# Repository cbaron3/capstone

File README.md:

# Capstone
Source code for Mechatronic Systems Engineering Capstone project

# Requirements

## Teensyduino

Firmware is written for a Teensy 3.2 and makes use of Teensy features such as PWMServo and elapsedMicros. 

[Teensyduino](https://www.pjrc.com/teensy/teensyduino.html)

## Barometer

Library to interact with the on-board MPL3115A2. 

[MPL3115A2](https://github.com/sparkfun/MPL3115A2_Breakout/tree/master/Libraries/Arduino)

## GPS

Libraries to interact with the on-board Adafruit GPS module. Two were selected: one interrupt-based and one polling-based. The interrupt-based library is what we use.

[Adafruit_GPS - Interrupt based](https://github.com/adafruit/Adafruit_GPS)

[TinyGPS - Polling based](https://github.com/mikalhart/TinyGPS)

## IMU

Library to interact with the on-board MPU9250.

[MPU9250](https://github.com/bolderflight/MPU9250)

## AHRS 

Library to filter our raw IMU data to produce accurate roll/pitch/yaw.

[uNavAHR](https://github.com/bolderflight/uNavAHRS)

[Eigen - Library Dependency](https://github.com/bolderflight/Eigen)

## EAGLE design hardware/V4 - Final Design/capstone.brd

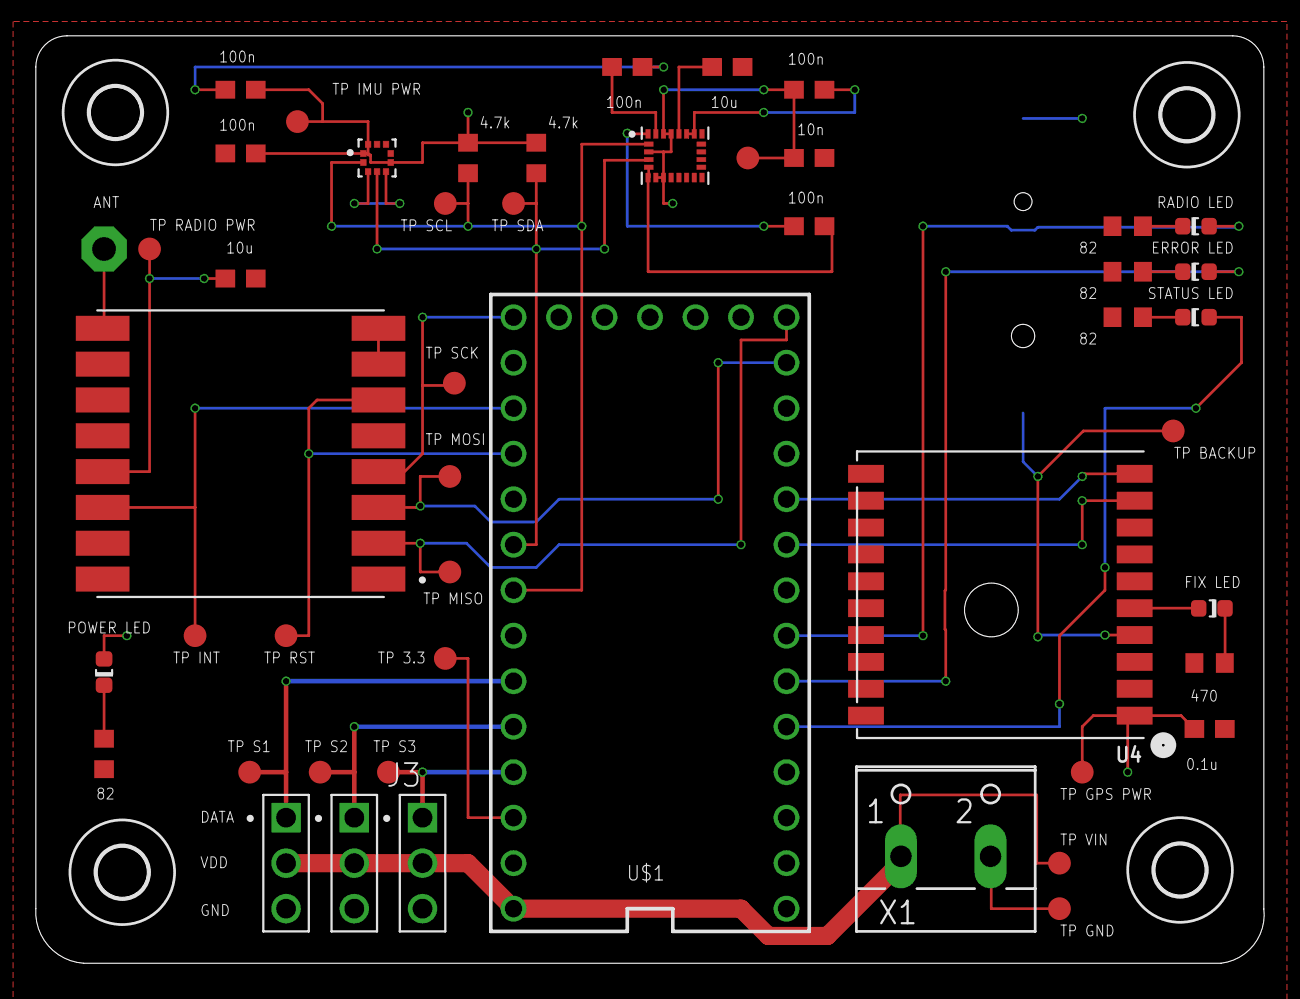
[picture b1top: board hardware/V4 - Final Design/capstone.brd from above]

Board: 2 copper layers, 68.6 x 51.8 mm, 54 parts (1 on the bottom side), 28 nets.

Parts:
ANT1: PAD-01
C1, C4: 10 u; C0603
C2: 100 n; C0603
C3: 0.1u; C0603
C5, C6: 100n; C0603
C7, C8: 100 nF; C0603
C9: 10 nF; C0603
G1: CH291-1220LF
H1, H2, H3, H4: MOUNT-HOLE2.8; 2,8
J1, J2, J3: 61300311121
LED1, LED2, LED3, LED4, LED5: HSMH-C190; LED-0603
R1, R2, R11, R12: 82 Ohm; R0603
R3, R4: 4.7k; R0603
R10: 470; R0603
TP1, TP2, TP3, TP4, TP5, TP6, TP7, TP8, TP9, TP10, TP11, TP12, TP13, TP14, TP15, TP16, TP17, TP18: PTR1B1,27; B1,27
U1: BMP388; PQFN50P200X200X80-10N
U2: LSM9DS1TR; PQFN43P300X350X102-24N
U3: RFM95W-915S2; XCVR_RFM95W-915S2
U4: FGPMMOPA6H
U$1: TEENSY_3.1-3.2_OUTER_ROW; TEENSY_3.0-3.2&LC_OUTER_ROW
X1: W237-102

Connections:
+3V3: C3.1, C4.1, C5.1, C6.1, C7.1, C8.1, C9.1, LED1.A, R3.1, R4.1, TP4.TP, TP8.TP, TP9.TP, TP11.TP, TP17.TP, U1.1, U1.6, U1.10, U2.1, U2.3, U2.7, U2.8, U2.22, U2.23, U3.13, U4.P$1, U$1.3.3V, U$1.3.3V1
ERR_LED: LED2.A, U$1.4
GND: C1.2, C2.2, C3.2, C4.2, C5.2, C6.2, C7.2, C8.2, C9.2, G1.-, J1.3, J2.3, J3.3, R1.2, R2.2, R10.1, R11.2, R12.2, TP16.TP, U1.3, U1.5, U1.8, U1.9, U2.5, U2.6, U2.19, U2.20, U3.1, U3.7, U3.8, U3.10, U3.11, U3.12, U3.15, U3.16, U4.P$3, U4.P$8, U4.P$12, U4.P$19, U$1.GND, U$1.GND1, X1.2
GPS_RX: U4.P$10, U$1.8
GPS_TX: U4.P$9, U$1.7
MISO: TP12.TP, U3.2, U$1.12
MOSI: TP18.TP, U3.3, U$1.11
unnamed: C1.1, U2.21
unnamed: C2.1, U2.24
unnamed: LED5.C, R10.2
unnamed: LED5.A, U4.P$5
unnamed: ANT1.1, U3.9
unnamed: LED1.C, R12.1
unnamed: LED2.C, R2.1
unnamed: LED4.C, R11.1
unnamed: LED3.C, R1.1
RADIO_INT: TP15.TP, U3.14, U$1.15/A1
RADIO_LED: LED4.A, U$1.5
RADIO_RST: TP14.TP, U3.6, U$1.16/A2
SCK: TP13.TP, U3.4, U$1.13
SCL: R4.2, TP2.TP, U1.2, U2.2, U$1.19/A5
SDA: R3.2, TP3.TP, U1.4, U2.4, U$1.18/A4
SERVO1: J1.1, TP5.TP, U$1.21/A7
SERVO2: J2.1, TP6.TP, U$1.22/A8
SERVO3: J3.1, TP7.TP, U$1.23/A9
STATUS_LED: LED3.A, U$1.3
VBACKUP: G1.+, TP10.TP, U4.P$4
VIN: J1.2, J2.2, J3.2, TP1.TP, U$1.VIN, X1.1

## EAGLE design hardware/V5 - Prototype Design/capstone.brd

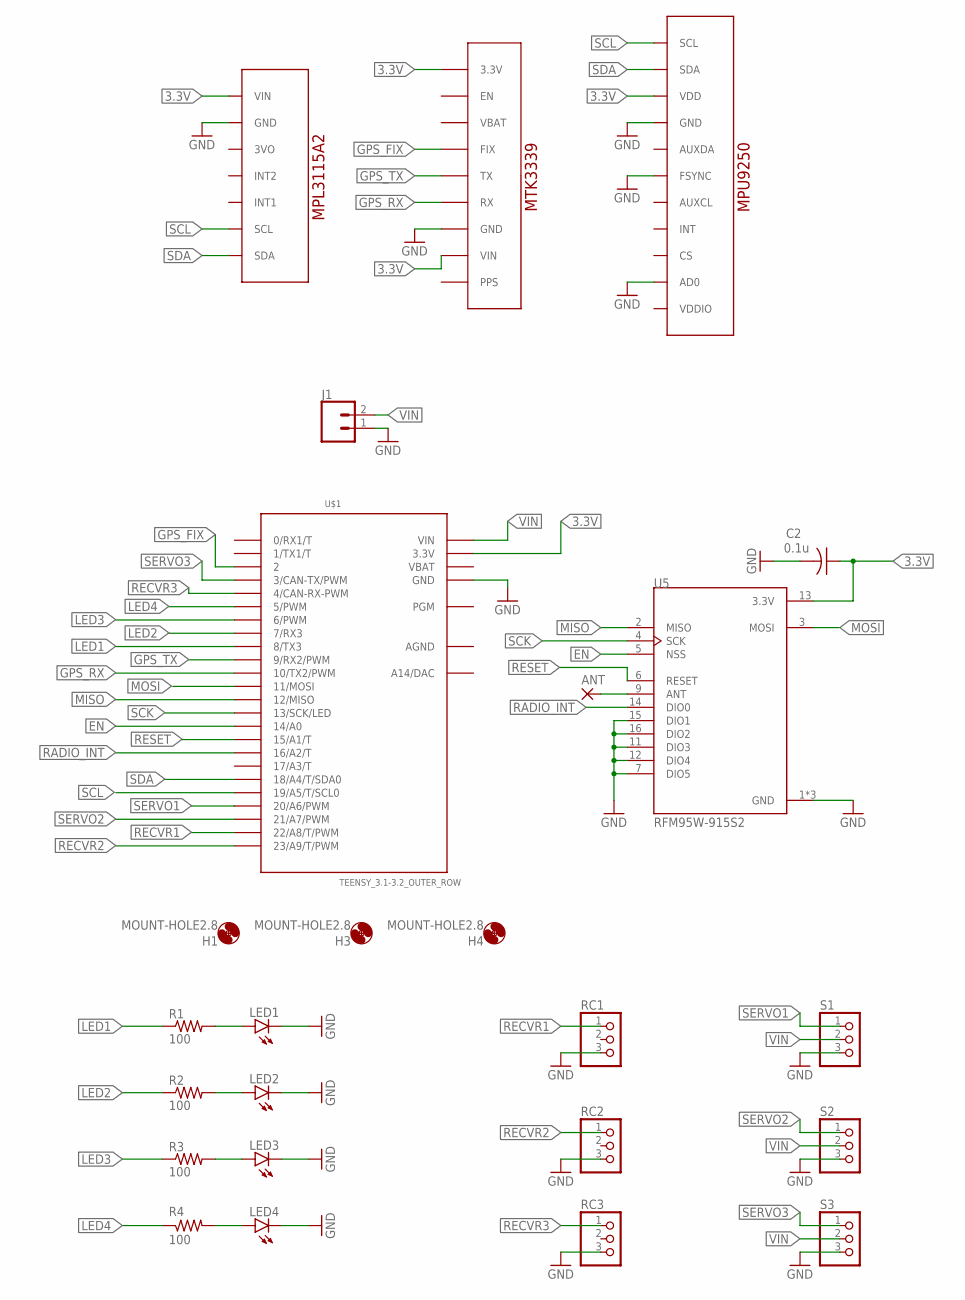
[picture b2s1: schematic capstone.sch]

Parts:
ANT: 2,54/0,9
C2: 0.1u; C1206
H1, H3, H4: MOUNT-HOLE2.8; 2,8
J1: CONN_025MM; SCREWTERMINAL-5MM-2
LED1, LED2, LED3, LED4: LEDCHIPLED_1206; CHIPLED_1206
R1, R2, R3, R4: 100; M1206
RC1, RC2, RC3: PINHD-1X3; 1X03
S1, S2, S3: PINHD-1X3; 1X03
U1: ADAFRUIT_MPL3115A2_BAROMETER
U2: ADAFRUIT_MTK3339_GPS
U4: SPARKFUN_MPU9250_IMU
U5: RFM95W-915S2; XCVR_RFM95W-915S2
U$1: TEENSY_3.1-3.2_OUTER_ROW; TEENSY_3.0-3.2&LC_OUTER_ROW

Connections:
3.3V: C2.1, U1.VIN, U2.3.3V, U2.VIN, U4.VDD, U5.13 (3.3V), U$1.3.3V, U$1.3.3V1 (3.3V)
AGND: U$1.AGND
EN: U5.5 (NSS), U$1.14/A0
GND: C2.2, J1.1, LED1.C, LED2.C, LED3.C, LED4.C, RC1.3, RC2.3, RC3.3, S1.3, S2.3, S3.3, U1.GND, U2.GND, U4.AD0, U4.FSYNC, U4.GND, U5.1 (GND), U5.7 (DIO5), U5.8 (GND), U5.10 (GND), U5.11 (DIO3), U5.12 (DIO4), U5.15 (DIO1), U5.16 (DIO2), U$1.GND, U$1.GND1 (GND)
GPS_FIX: U2.FIX, U$1.2
GPS_RX: U2.RX, U$1.10 (10/TX2/PWM)
GPS_TX: U2.TX, U$1.9 (9/RX2/PWM)
LED1: R1.1, U$1.8 (8/TX3)
LED2: R2.1, U$1.7 (7/RX3)
LED3: R3.1, U$1.6 (6/PWM)
LED4: R4.1, U$1.5 (5/PWM)
MISO: U5.2 (MISO), U$1.12 (12/MISO)
MOSI: U5.3 (MOSI), U$1.11 (11/MOSI)
unnamed: ANT.1, U5.9 (ANT)
unnamed: LED1.A, R1.2
unnamed: LED2.A, R2.2
unnamed: LED3.A, R3.2
unnamed: LED4.A, R4.2
RADIO_INT: U5.14 (DIO0), U$1.16/A2 (16/A2/T)
RECVR1: RC1.1, U$1.22/A8 (22/A8/T/PWM)
RECVR2: RC2.1, U$1.23/A9 (23/A9/T/PWM)
RECVR3: RC3.1, U$1.4 (4/CAN-RX-PWM)
RESET: U5.6 (RESET), U$1.15/A1 (15/A1/T)
SCK: U5.4 (SCK), U$1.13 (13/SCK/LED)
SCL: U1.SCL, U4.SCL, U$1.19/A5 (19/A5/T/SCL0)
SDA: U1.SDA, U4.SDA, U$1.18/A4 (18/A4/T/SDA0)
SERVO1: S1.1, U$1.20/A6 (20/A6/PWM)
SERVO2: S2.1, U$1.21/A7 (21/A7/PWM)
SERVO3: S3.1, U$1.3 (3/CAN-TX/PWM)
VBAT: U$1.VBAT
VIN: J1.2, S1.2, S2.2, S3.2, U$1.VIN

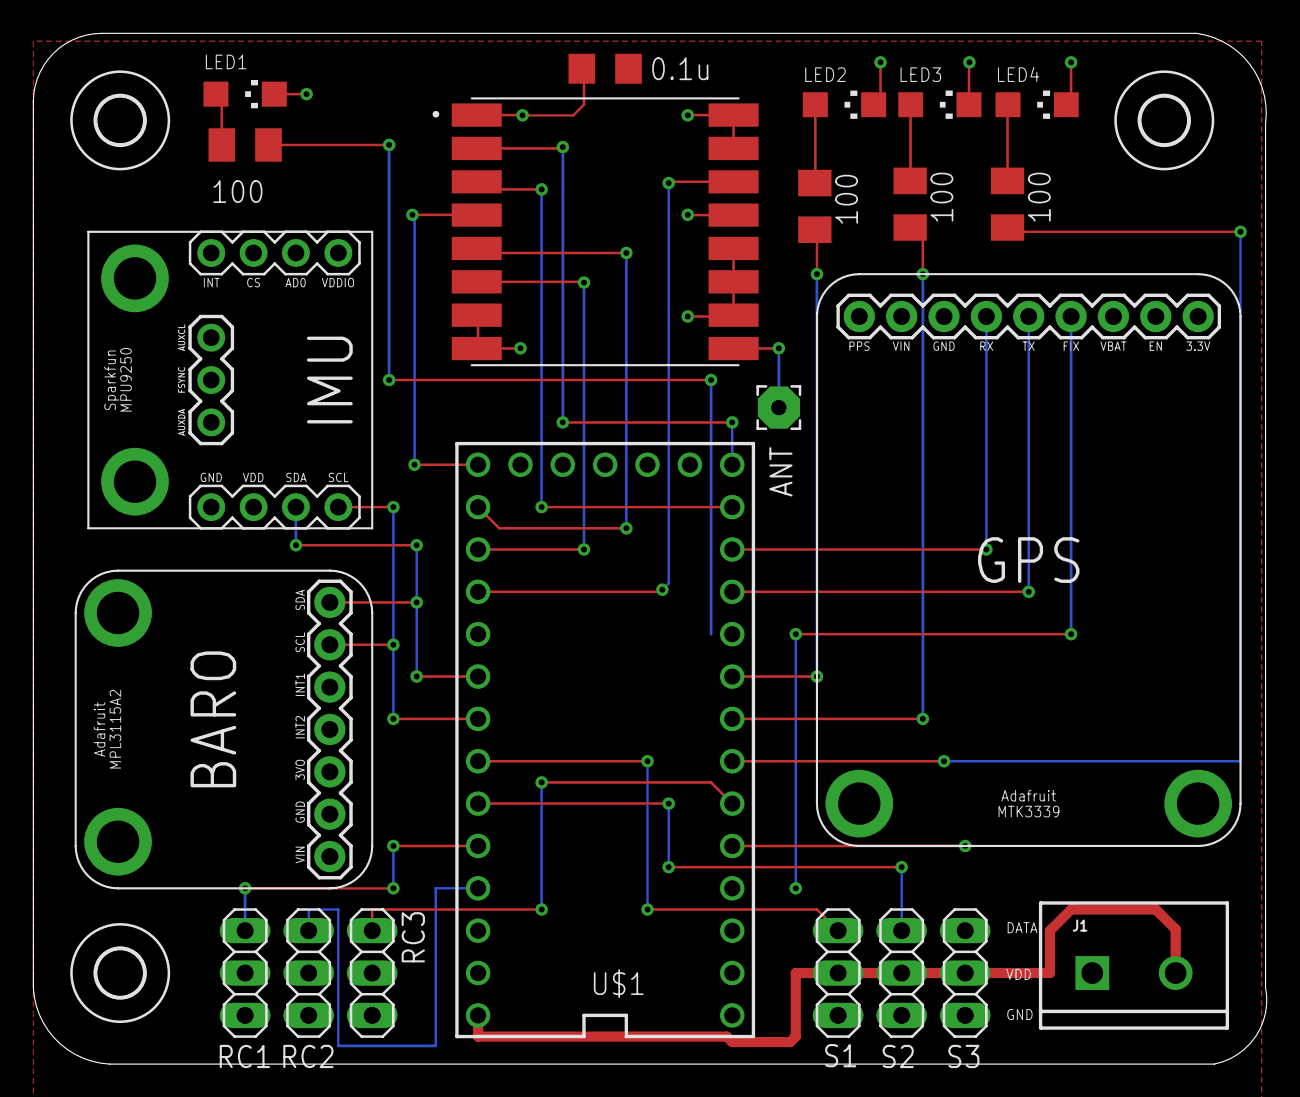
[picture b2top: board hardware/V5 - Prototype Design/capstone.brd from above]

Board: 2 copper layers, 74.0 x 61.8 mm, 25 parts (0 on the bottom side), 29 nets.

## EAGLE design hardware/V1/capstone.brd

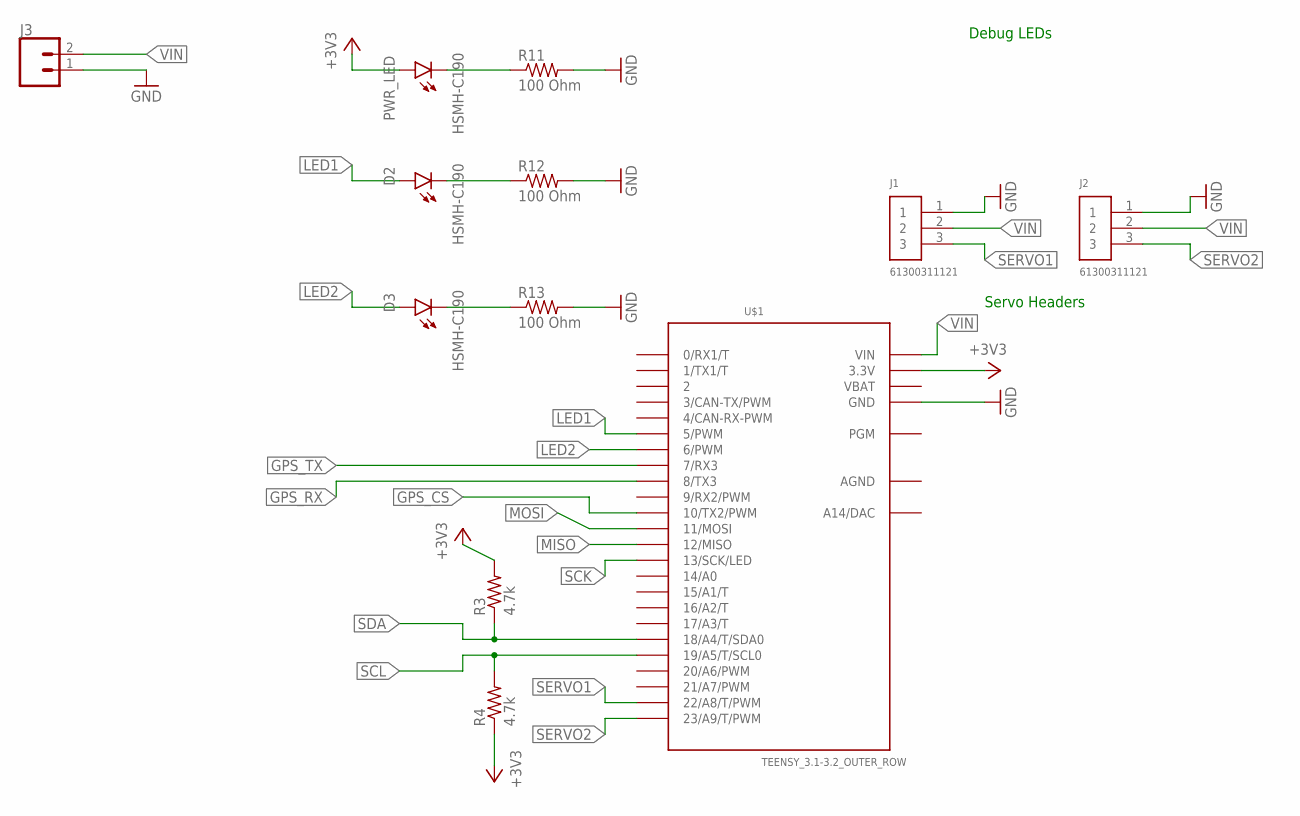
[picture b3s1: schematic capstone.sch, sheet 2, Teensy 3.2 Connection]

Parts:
D2, D3: HSMH-C190; LED-0603
J1, J2: 61300311121
J3: CONN_02; 1X02
PWR_LED: HSMH-C190; LED-0603
R3, R4: 4.7k; R0603
R11, R12, R13: 100 Ohm; R0603
U$1: TEENSY_3.1-3.2_OUTER_ROW; TEENSY_3.0-3.2&LC_OUTER_ROW

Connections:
+3V3: PWR_LED.A, R3.2, R4.1, U$1.3.3V, U$1.3.3V1 (3.3V); also elsewhere on the board
AGND: U$1.AGND
GND: J1.1, J2.1, J3.1, R11.2, R12.2, R13.2, U$1.GND, U$1.GND1 (GND); also elsewhere on the board
GPS_CS: U$1.10 (10/TX2/PWM); also elsewhere on the board
GPS_RX: U$1.8 (8/TX3); also elsewhere on the board
GPS_TX: U$1.7 (7/RX3); also elsewhere on the board
LED1: D2.A, U$1.5 (5/PWM)
LED2: D3.A, U$1.6 (6/PWM)
MISO: U$1.12 (12/MISO); also elsewhere on the board
MOSI: U$1.11 (11/MOSI); also elsewhere on the board
unnamed: PWR_LED.C, R11.1
unnamed: D2.C, R12.1
unnamed: D3.C, R13.1
SCK: U$1.13 (13/SCK/LED); also elsewhere on the board
SCL: R4.2, U$1.19/A5 (19/A5/T/SCL0); also elsewhere on the board
SDA: R3.1, U$1.18/A4 (18/A4/T/SDA0); also elsewhere on the board
SERVO1: J1.3, U$1.22/A8 (22/A8/T/PWM)
SERVO2: J2.3, U$1.23/A9 (23/A9/T/PWM)
VBAT: U$1.VBAT
VIN: J1.2, J2.2, J3.2, U$1.VIN

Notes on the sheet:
Servo Headers
Debug LEDs

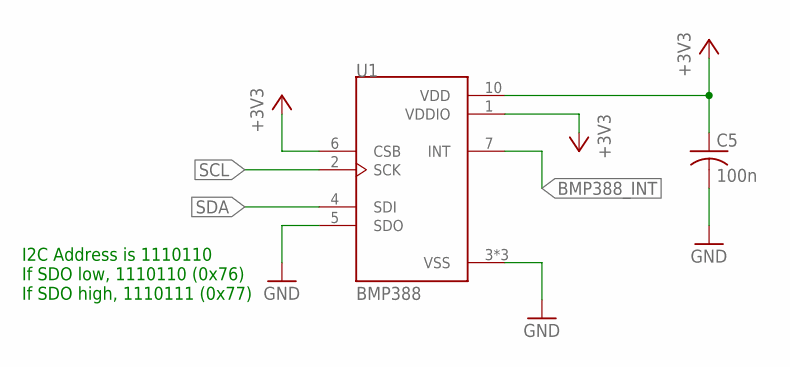
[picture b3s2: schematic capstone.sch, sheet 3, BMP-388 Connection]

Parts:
C5: 100n; C0603
U1: BMP388; PQFN50P200X200X80-10N

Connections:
+3V3: C5.1, U1.1 (VDDIO), U1.6 (CSB), U1.10 (VDD); also elsewhere on the board
BMP388_INT: U1.7 (INT)
GND: C5.2, U1.3 (VSS), U1.5 (SDO), U1.8 (VSS), U1.9 (VSS); also elsewhere on the board
SCL: U1.2 (SCK); also elsewhere on the board
SDA: U1.4 (SDI); also elsewhere on the board

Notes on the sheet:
I2C Address is 1110110 If SDO low, 1110110 (0x76) If SDO high, 1110111 (0x77)

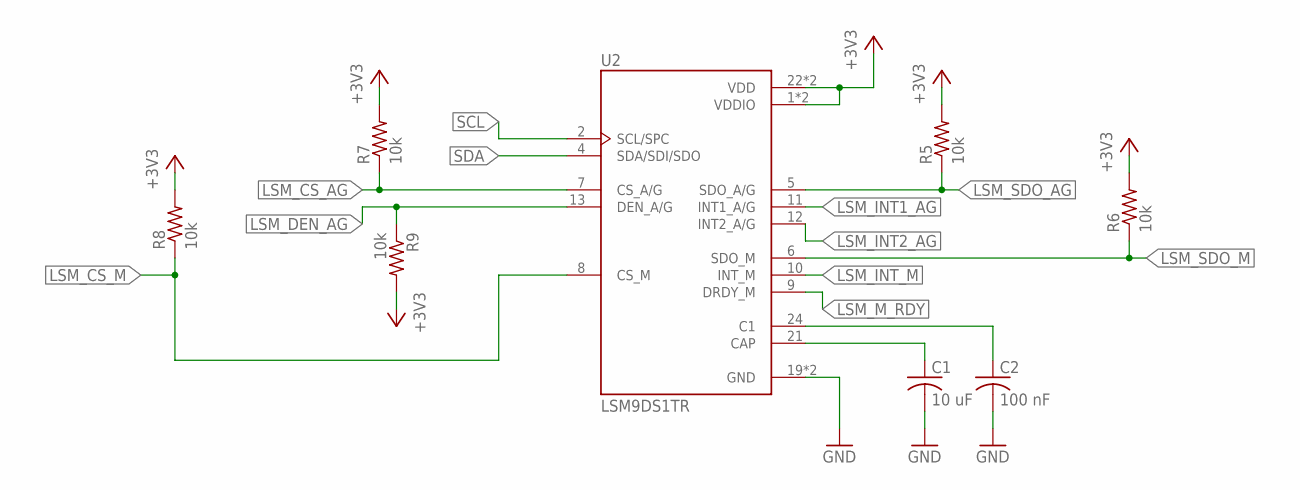
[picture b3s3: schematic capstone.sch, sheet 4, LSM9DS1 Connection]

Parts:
C1: 10 uF; C0603
C2: 100 nF; C0603
R5, R6, R7, R8, R9: 10k; R0603
U2: LSM9DS1TR; PQFN43P300X350X102-24N

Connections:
+3V3: R5.2, R6.2, R7.2, R8.2, R9.2, U2.1 (VDDIO), U2.3 (VDDIO), U2.22 (VDD), U2.23 (VDD); also elsewhere on the board
GND: C1.2, C2.2, U2.19 (GND), U2.20 (GND); also elsewhere on the board
LSM_CS_AG: R7.1, U2.7 (CS_A/G)
LSM_CS_M: R8.1, U2.8 (CS_M)
LSM_DEN_AG: R9.1, U2.13 (DEN_A/G)
LSM_INT1_AG: U2.11 (INT1_A/G)
LSM_INT2_AG: U2.12 (INT2_A/G)
LSM_INT_M: U2.10 (INT_M)
LSM_M_RDY: U2.9 (DRDY_M)
LSM_SDO_AG: R5.1, U2.5 (SDO_A/G)
LSM_SDO_M: R6.1, U2.6 (SDO_M)
unnamed: C1.1, U2.21 (CAP)
unnamed: C2.1, U2.24 (C1)
SCL: U2.2 (SCL/SPC); also elsewhere on the board
SDA: U2.4 (SDA/SDI/SDO); also elsewhere on the board

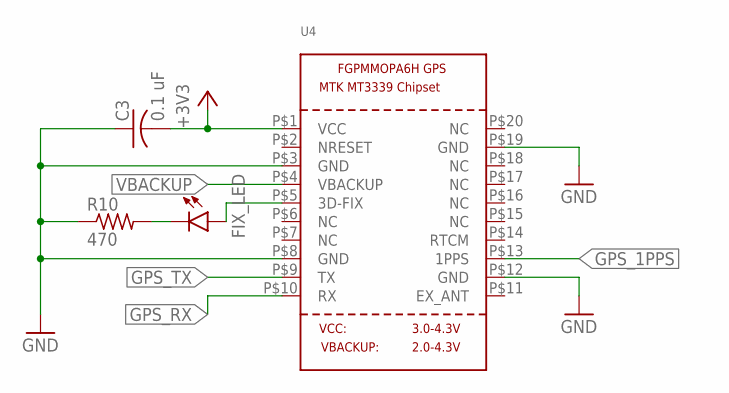
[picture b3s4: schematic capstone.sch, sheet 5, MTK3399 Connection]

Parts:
C3: 0.1 uF; C0603
FIX_LED: HSMH-C190; LED-0603
R10: 470; R0603
U4: GPS_FGPMMOPA6H; FGPMMOPA6H

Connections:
+3V3: C3.2, U4.P$1 (VCC); also elsewhere on the board
GND: C3.1, R10.1, U4.P$3 (GND), U4.P$8 (GND), U4.P$12 (GND), U4.P$19 (GND); also elsewhere on the board
GPS_1PPS: U4.P$13 (1PPS)
GPS_RX: U4.P$10 (RX); also elsewhere on the board
GPS_TX: U4.P$9 (TX); also elsewhere on the board
unnamed: FIX_LED.C, R10.2
unnamed: FIX_LED.A, U4.P$5 (3D-FIX)
VBACKUP: U4.P$4 (VBACKUP)

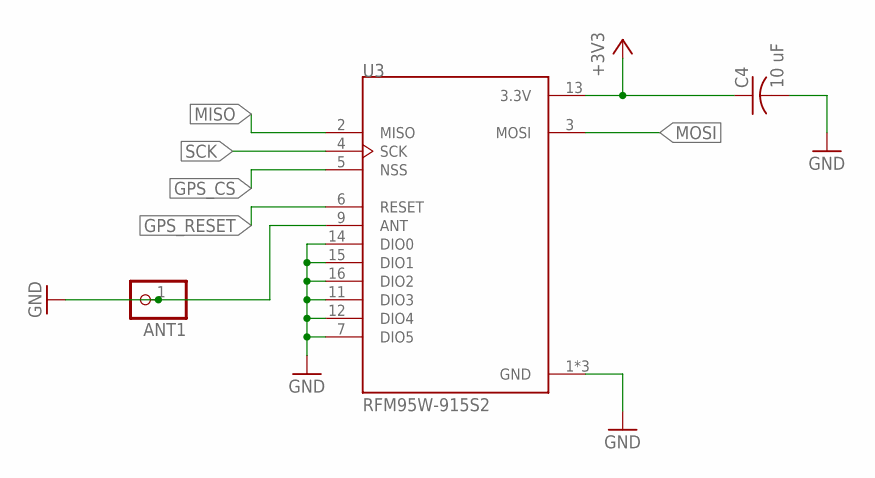
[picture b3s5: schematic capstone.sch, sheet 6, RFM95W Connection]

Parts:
ANT1: PINHD-1X1; 1X01
C4: 10 uF; C0603
U3: RFM95W-915S2; XCVR_RFM95W-915S2

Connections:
+3V3: C4.1, U3.13 (3.3V); also elsewhere on the board
GND: ANT1.1, C4.2, U3.1 (GND), U3.7 (DIO5), U3.8 (GND), U3.9 (ANT), U3.10 (GND), U3.11 (DIO3), U3.12 (DIO4), U3.14 (DIO0), U3.15 (DIO1), U3.16 (DIO2); also elsewhere on the board
GPS_CS: U3.5 (NSS); also elsewhere on the board
GPS_RESET: U3.6 (RESET)
MISO: U3.2 (MISO); also elsewhere on the board
MOSI: U3.3 (MOSI); also elsewhere on the board
SCK: U3.4 (SCK); also elsewhere on the board

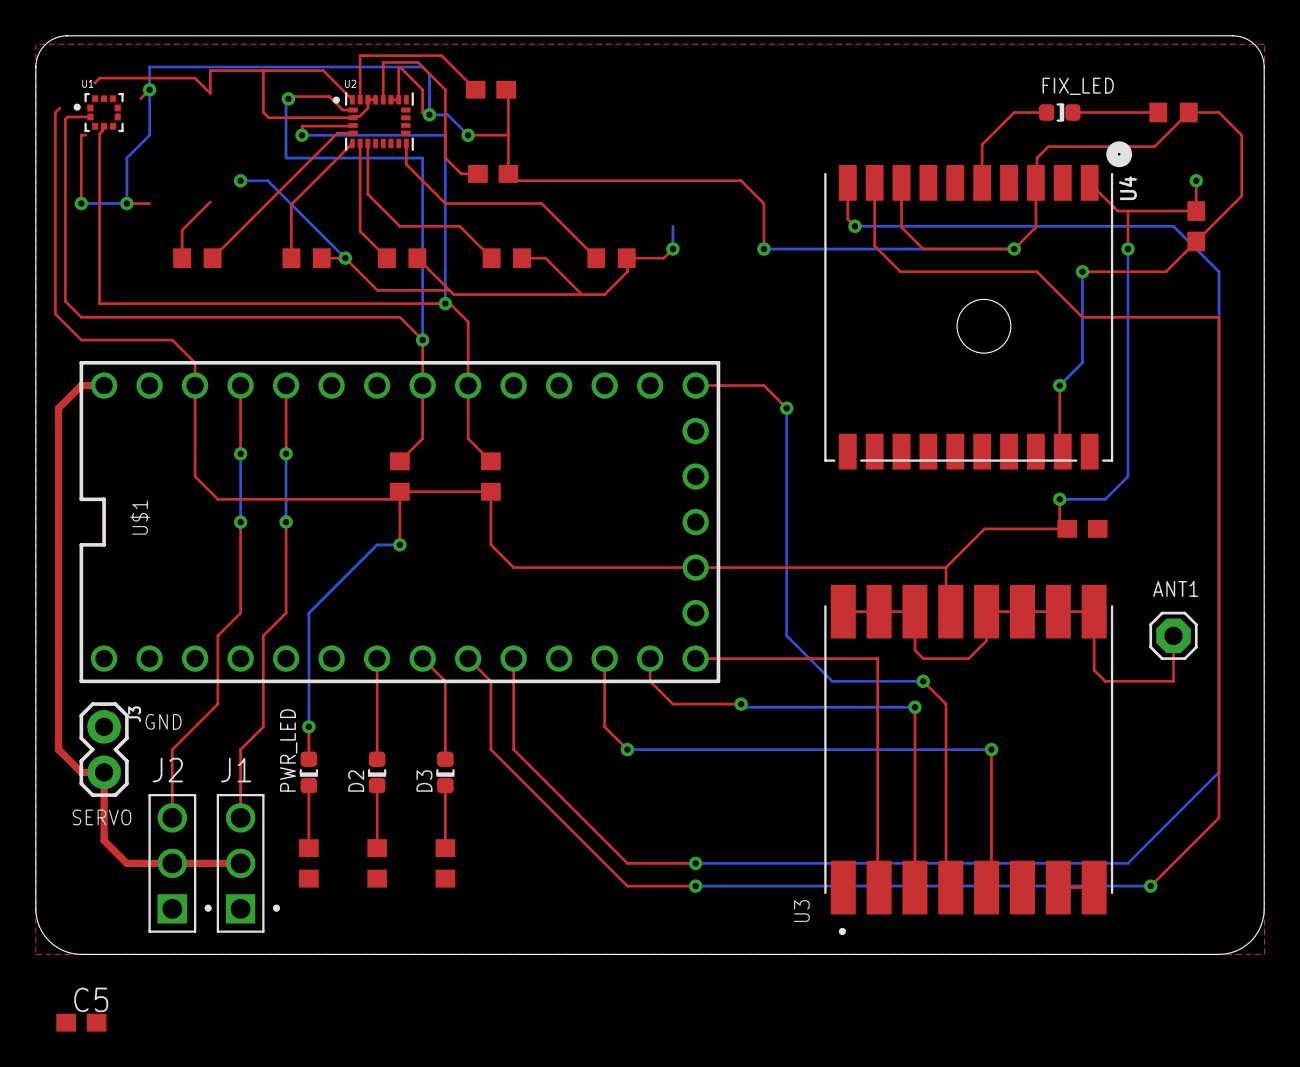
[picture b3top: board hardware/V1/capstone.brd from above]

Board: 2 copper layers, 68.6 x 51.3 mm, 29 parts (0 on the bottom side), 27 nets.

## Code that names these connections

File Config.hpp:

#pragma once

/**
 * File for containing all configuration variables such as pins, constants
 */
 
#include "Arduino.h"
#include "src/aero-cpp-lib/include/Data.hpp"


using Pin = unsigned int;

static constexpr float TARGET_LAT = 0.0f;
static constexpr float TARGET_LON = 0.0f;
static constexpr float TARGET_ALT = 0.0f;

enum mode_type {MODE_IDLE = 0, MODE_MANUAL = 1, MODE_AUTO = 2, MODE_SAFETY = 3};
static constexpr mode_type DEFAULT_MODE = MODE_AUTO;

// Commands
static constexpr uint8_t CMD_PITCH_UP_GLIDER1 = 0x00; // Glider 1 Emergency Pitch Up; Only if this device is G1.
static constexpr uint8_t CMD_PITCH_UP_GLIDER2 = 0x01; // Glider 2 Emergency Pitch Up; Only if this device is G2.
static constexpr uint8_t CMD_TOGGLE_ENGAGE    = 0x05;
static constexpr uint8_t CMD_COMMS_TEST       = 0x06; // Glider Communications Check. Can also be used to send back data.
static constexpr uint8_t CMD_MODE_SWAP        = 0x07; // Glider Mode Swap. Auto/Manual mode toggle.

static constexpr uint8_t STATE_GPS_FIX = 0x00; // Bit 0 for GPS fix
static constexpr uint8_t STATE_ENGAGED_MODE = 0x1E; // Bit 30 for engage mode
static constexpr uint8_t STATE_UNDEFINED_MODE = 0x1F; // Bit 31 for undefined mode

static constexpr float ALLOWABLE_AZIMUTH_ERROR = 3.0f;
static constexpr float ALLOWABLE_ELEVATION_ERROR = 3.0f;

#define  DEBUG
//#define  VERBOSE_DEBUG
//#define  TEST_TRAINER
#define FINAL_GLIDER

#ifdef DEBUG
    #define DEBUG_PRINT(x) Serial.print(x)
    #define DEBUG_PRINTLN(x) Serial.println(x)
    #define DEBUG_START(x) Serial.begin(x); delay(1000)
#else
    #define DEBUG_PRINT(x)
    #define DEBUG_PRINTLN(x)
    #define DEBUG_START(x)
#endif

#if defined(FINAL_GLIDER)
    static constexpr unsigned long LEFT_ELEVON_MS_OFFSET = 0;
    static constexpr unsigned long RIGHT_ELEVON_MS_OFFSET = 0;

    static constexpr float SERVO_MIN_MS = 800.0f;
    static constexpr float SERVO_MAX_MS = 2000.0f;

#elif defined(TEST_GLIDER)
    static constexpr unsigned long LEFT_ELEVON_MS_OFFSET = 0;
    static constexpr unsigned long RIGHT_ELEVON_MS_OFFSET = 0;

    static constexpr float SERVO_MIN_MS = 800.0f;
    static constexpr float SERVO_MAX_MS = 2000.0f;

#elif defined(TEST_TRAINER)
    static constexpr unsigned long LEFT_ELEVON_MS_OFFSET = 40;   // Pitch
    static constexpr unsigned long RIGHT_ELEVON_MS_OFFSET = 50; // Roll

    static constexpr float SERVO_MIN_MS = 900.0f;
    static constexpr float SERVO_MAX_MS = 2100.0f;
#else 
    static constexpr unsigned long LEFT_ELEVON_MS_OFFSET = 0;
    static constexpr unsigned long RIGHT_ELEVON_MS_OFFSET = 0;

    static constexpr float SERVO_MIN_MS = 800.0f;
    static constexpr float SERVO_MAX_MS = 2000.0f;
#endif

/* DEVICE NAMES */
const String NAMES[] = {"GND", "PLANE", "G1", "G2"};

/* CALIBRATION FLAGS */
static constexpr bool CALIBRATE_ACCEL = false;
static constexpr bool CALIBRATE_GYRO = true;
static constexpr bool CALIBRATE_MAG = false;
static constexpr bool CALIBRATE_BARO = true;

/* BOOT MODE */ 
enum class BOOT_MODE {LED_TEST, LED_TEST_RANDOM};
static constexpr BOOT_MODE MODE = BOOT_MODE::LED_TEST_RANDOM;

/* PID */
static constexpr double ROLL_KP = 3.0f, ROLL_KI = 0.00f, ROLL_KD = 0.0f;
static constexpr double PITCH_KP = 8.0f, PITCH_KI = 0.00f, PITCH_KD = 0.0f;
static constexpr double YAW_KP = 1.0f, YAW_KI = 0.00f, YAW_KD = 0.0f;

static constexpr double DEFAULT_ROLL_SETPOINT = 0;
static constexpr double ROLL_MIN_LIMIT = -90;
static constexpr double ROLL_MAX_LIMIT = 90;

static constexpr double DEFAULT_PITCH_SETPOINT = 8;
static constexpr double PITCH_MIN_LIMIT = -90;
static constexpr double PITCH_MAX_LIMIT = 90;

static constexpr double DEFAULT_YAW_SETPOINT = 0;
static constexpr double YAW_MIN_LIMIT = -90;
static constexpr double YAW_MAX_LIMIT = 90;

static constexpr bool INVERT_PID = true;

/* BAROMETER */
static constexpr double ALTITUDE_BIAS = 238.0f; // In metres

// Sampling intervals of 0=6 ms , 1=10, 2=18, 3=34, 4=66, 5=130, 6=258, and 7=512
static constexpr unsigned long OVER_SAMPLE_PERIODS_MS[] = {6, 10, 18, 34, 66, 130, 258, 512};
static constexpr int OVER_SAMPLE_RATIO = 7;

/* SYSTEM FLAGS */
static constexpr bool DEBUG_MODE = true;  // Block usage of Serial printing if not debugging to speed up system

/* LEDS */
static constexpr Pin LED1 = 8;
static constexpr Pin LED2 = 7;
static constexpr Pin LED3 = 6;
static constexpr Pin LED4 = 5;
static constexpr unsigned int LED_COUNT = 4;
static constexpr Pin LED_PINS[LED_COUNT] = {LED1, LED2, LED3, LED4};

/* FROM LEFT TO RIGHT */
static constexpr Pin POWER_LED = LED1;    // On when board is powered
static constexpr Pin ACTIVITY_LED = LED2; // Toggles on and off to signal that the CPU is running
static constexpr Pin RADIO_LED = LED3;    // Turns on when new message is received
static constexpr Pin MODE_LED = LED4;     // On when in manual mode, else off

/* SERVOS */
static constexpr Pin SERVO1 = 20;
static constexpr Pin SERVO2 = 21;
static constexpr Pin SERVO3 = 3;
static constexpr Pin SERVOS[] = {SERVO1, SERVO2, SERVO3};

static constexpr float SERVO_MIN_ANGLE = 0.0f;
static constexpr float SERVO_MAX_ANGLE = 179.0f;

const int RADIO_ID = 0;
const int GPS_ID = 1;
const int I2C_ID = 2;
const int SETPOINT_ID = 3;
const int AUTO_ID = 4;
const int MANUAL_ID = 5;
const int ACTIVITY_ID = 6;
const int DEBUG_ID = 7;

// For fixed wing trainer
static constexpr int DEFAULT_LEFT_ELEVON_ANGLE = 90;
static constexpr int DEFAULT_RIGHT_ELEVON_ANGLE = 90;
static constexpr int DEFAULT_RUDDER_ANGLE = 90;

static constexpr int SAFETY_LEFT_ELEVON_ANGLE = 180;
static constexpr int SAFETY_RIGHT_ELEVON_ANGLE = 0;
static constexpr int SAFETY_RUDDER_ANGLE = 90;


/* RECEIVER INPUTS */
static constexpr Pin RECEIVER1 = 22;   // Left elevon
static constexpr Pin RECEIVER2 = 23;  // Right elevon
static constexpr Pin RECEIVER3 = 4;   // Rudder
static constexpr Pin RECEIVERS[] = {RECEIVER1, RECEIVER2, RECEIVER3};

/* RADIO */
static constexpr Pin RADIO_CS = 14;
static constexpr Pin RADIO_RESET = 15;
static constexpr Pin RADIO_INT = 16;
static constexpr float RADIO_FREQ = 905.0f;
static constexpr int RADIO_POWER = 23;

static constexpr aero::def::ID THIS_DEVICE = aero::def::ID::G2;

// Glider 1
float g1_axb = 0.0f;
float g1_axs = 0.0f;
float g1_ayb = 0.0f;
float g1_ays = 0.0f;
float g1_azb = 0.0f;
float g1_azs = 0.0f;

float g1_mxb = 0.0f;
float g1_mxs = 0.0f;
float g1_myb = 0.0f;
float g1_mys = 0.0f;
float g1_mzb = 0.0f;
float g1_mzs = 0.0f;

// Glider 2
float g2_axb = 0.0f;
float g2_axs = 0.0f;
float g2_ayb = 0.0f;
float g2_ays = 0.0f;
float g2_azb = 0.0f;
float g2_azs = 0.0f;

float g2_mxb = 0.0f;
float g2_mxs = 0.0f;
float g2_myb = 0.0f;
float g2_mys = 0.0f;
float g2_mzb = 0.0f;
float g2_mzs = 0.0f;


template <class X, class M, class N, class O, class Q>
inline X map_generic(X x, M in_min, N in_max, O out_min, Q out_max){
  return (x - in_min) * (out_max - out_min) / (in_max - in_min) + out_min;
}

template <class A, class B, class C>
inline A constrain_generic(A a, B in_min, C in_max) {
  if(a <= in_max && a >= in_min) {
    return a;
  } else if(a >= in_max) {
    return in_max;
  } else {
    return in_min;
  }
}

/* GPS */
static constexpr HardwareSerial *GPS_PORT = &Serial2;
static constexpr Pin GPS_FIX =  4;

/* DELAYS */
const long GPS_INTERVAL_MS = 1000;
const unsigned long THREAD_DELAY_MS = 1000;
const unsigned long DEBUG_INTERVAL_MS = 250;
const unsigned long IMU_SAMPLE_INTERVAL_MS = 20;
const unsigned long RADIO_INTERVAL_MS = 250;
const unsigned long MANUAL_INTERVAL_MS = 20;    // 50 HZ Servos
const unsigned long AUTO_INTERVAL_MS = 10;      // 50 HZ Servos
static constexpr int BARO_SAMPLE_INTERVAL_MS = OVER_SAMPLE_PERIODS_MS[OVER_SAMPLE_RATIO];

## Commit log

2019-11-16 Added basic libraries
2019-11-16 First revision of schematic
2019-11-17 Finished board routing
2019-12-02 Finalize board
2020-01-08 new board
2020-01-10 added manufacturing files
2020-01-17 cleared previous code for new start
2020-01-17 Basic led test and working on receiver interrupt code
2020-01-17 Setup libraries
2020-01-22 Added sensor support, servo support, led support, and filtering
2020-01-22 code cleanup
2020-01-24 added pid
2020-01-25 radio setup
2020-01-26 thread setup; radio comms
2020-01-28 version 3 of the board; hooked up interrupt pin and added an extra servo
2020-01-30 trying to get submodule pulled
2020-01-31 mode swapping
2020-01-31 mode swap tested, seems to be working
2020-01-31 pitch command
2020-02-05 basic servo working; also added gerber files
2020-02-06 proved that auto/manual mode works
2020-02-06 more code cleanup
2020-02-06 more code cleanup cause perfectionism
2020-02-10 testing session 1
2020-02-10 added baro calibration
2020-02-11 playing around with constants and values for fixed wing model
2020-02-11 code cleanup and simplification
2020-02-12 added screw terminal to board; combined filter with imu scope
2020-02-12 imu refractoring; code not compiling
2020-02-12 code compiling for imu now; need to test
2020-02-13 verified v4 - final design pins and started clean up for report
2020-02-15 board update
2020-02-16 getting imu to work again
2020-02-16 testing
2020-02-16 Schematic Cleanup
2020-02-16 add test points to final design
2020-02-16 finalized board design for final design
2020-02-17 updated glider design circuit board
2020-02-24 design update for hardware
2020-02-24 code cleanup to appease the capstone gods
2020-02-29 added state machine for glider. idle, auto, manual, safety
2020-03-02 temp, saving setpoint work
2020-03-02 setpoint and pitch up written
2020-03-30 competition update

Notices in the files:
parts and their libraries:
SparkFun-Connectors: Licensing: Creative Commons ShareAlike 4.0 International - https://creativecommons.org/licenses/by-sa/4.0
